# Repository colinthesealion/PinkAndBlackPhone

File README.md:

PinkAndBlackPhone
=================

PCB Designs for the Pink &amp; Black Phone

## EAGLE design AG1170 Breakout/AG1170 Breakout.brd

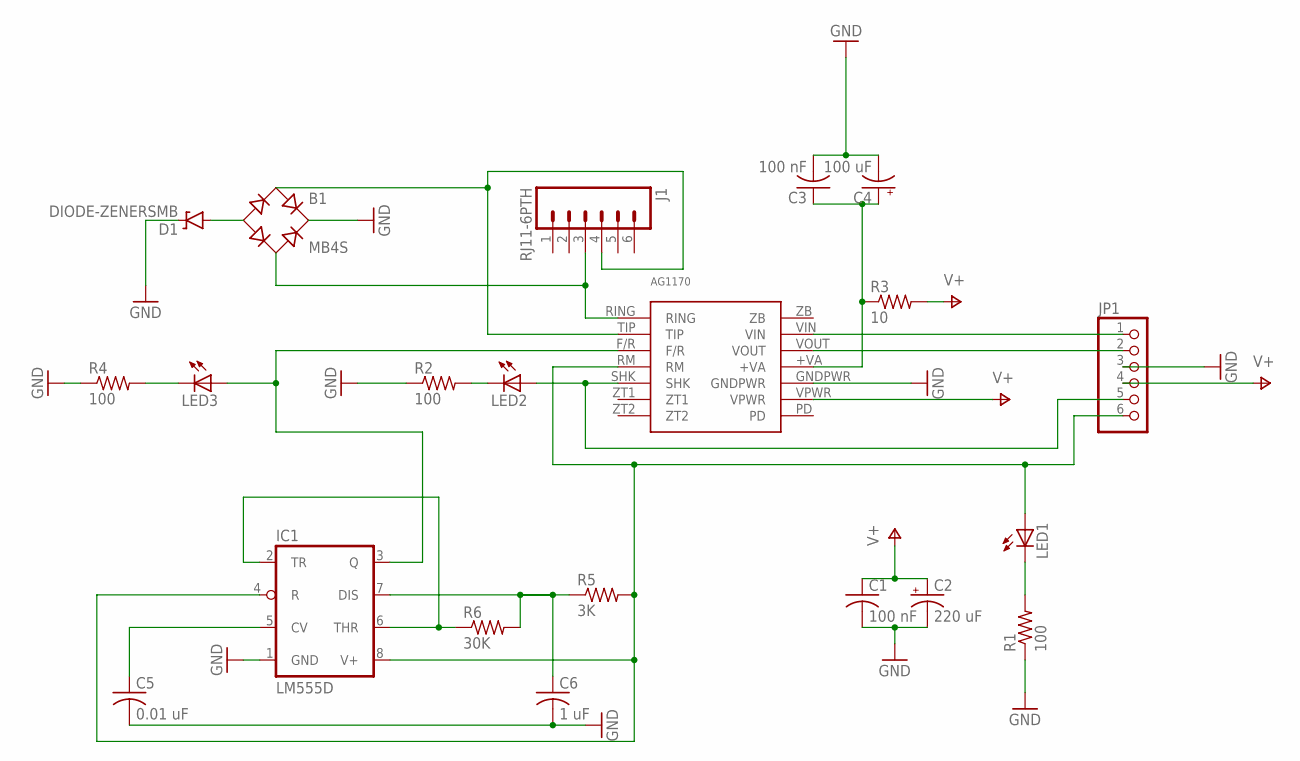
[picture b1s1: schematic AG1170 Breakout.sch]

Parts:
AG1170: AG1170
B1: MB4S; SOIC-4
C1, C3: 100 nF; C0805
C2: 220 uF; EIA3216
C4: 100 uF; EIA3216
C5: 0.01 uF; C0805
C6: 1 uF; C0805
D1: DIODE-ZENERSMB; SMB-DIODE
IC1: LM555D; SO08
J1: RJ11-6PTH; RJ11-6
JP1: PINHD-1X6; 1X06
LED1, LED2, LED3: LEDCHIP-LED0805; CHIP-LED0805
R1, R2, R4: 100; R0805
R3: 10; R0805
R5: 3K; R0805
R6: 30K; R0805

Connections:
GND: AG1170.GNDPWR, B1.+, C1.2, C2.C (-), C3.2, C4.C (-), C5.2, C6.2, D1.C, IC1.1 (GND), JP1.3, R1.1, R2.1, R4.1
unnamed: LED1.C, R1.2
unnamed: LED2.C, R2.2
unnamed: AG1170.SHK, JP1.5, LED2.A
unnamed: AG1170.+VA, C3.1, C4.A (+), R3.1
unnamed: LED3.C, R4.2
unnamed: AG1170.RM, IC1.4 (R), IC1.8 (V+), JP1.6, LED1.A, R5.2
unnamed: AG1170.VIN, JP1.1
unnamed: AG1170.VOUT, JP1.2
unnamed: AG1170.RING, B1.~2 (AC2), J1.3
unnamed: AG1170.TIP, B1.~1 (AC1), J1.4
unnamed: AG1170.F/R, IC1.3 (Q), LED3.A
unnamed: B1.-, D1.A
unnamed: IC1.2 (TR), IC1.6 (THR), R6.1
unnamed: C6.1, IC1.7 (DIS), R5.1, R6.2
unnamed: C5.1, IC1.5 (CV)
V+: AG1170.VPWR, C1.1, C2.A (+), JP1.4, R3.2

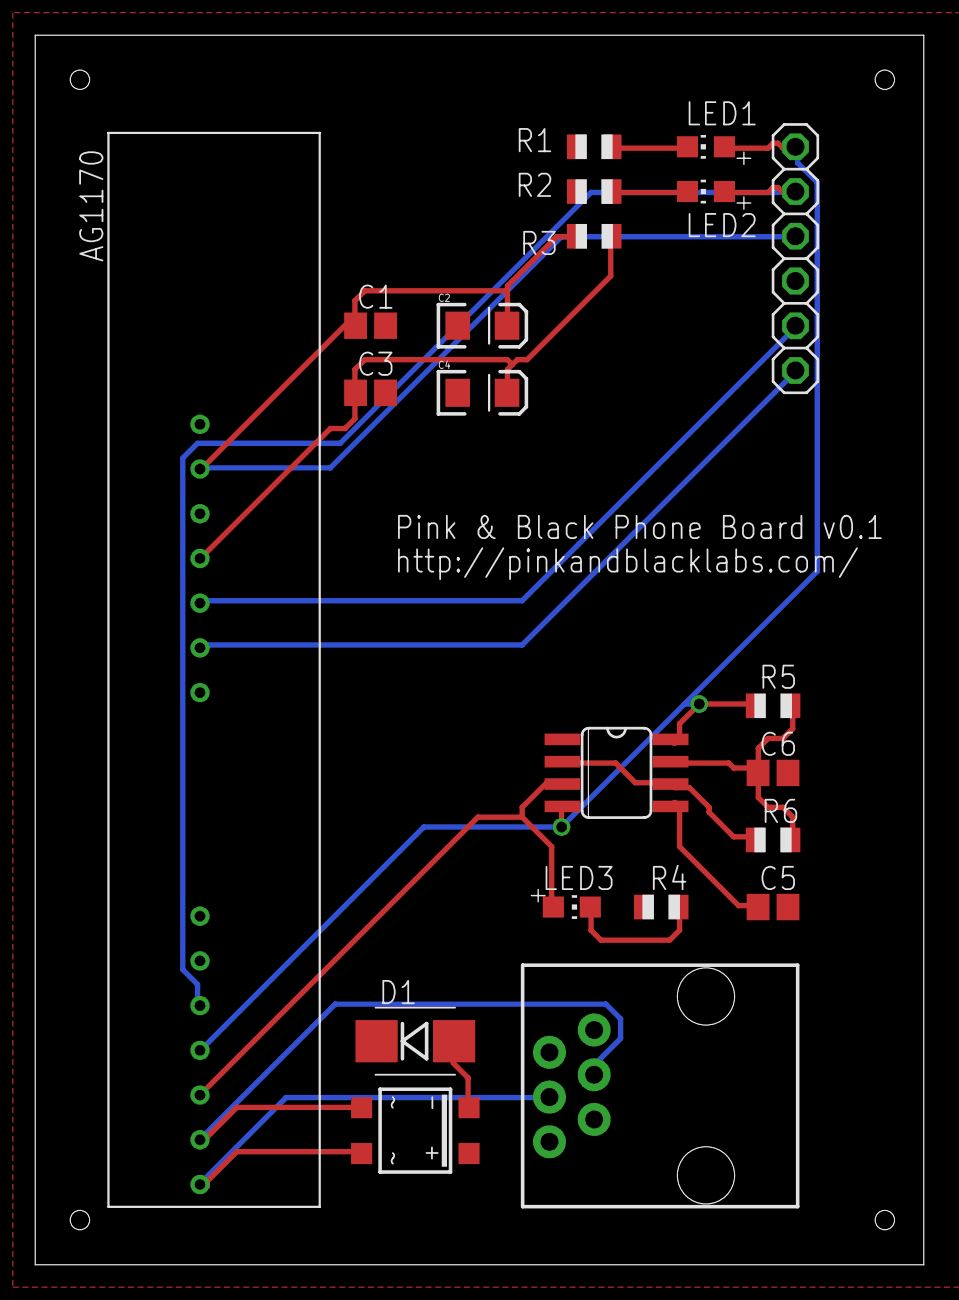
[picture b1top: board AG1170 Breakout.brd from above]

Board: 2 copper layers, 50.5 x 69.8 mm, 21 parts (0 on the bottom side), 17 nets.

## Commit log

2014-07-27 Initial import
2014-07-27 Add schematic for breakout board

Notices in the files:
parts and their libraries:
SparkFun-Capacitors: Licensing: Creative Commons ShareAlike 4.0 International - https://creativecommons.org/licenses/by-sa/4.0
